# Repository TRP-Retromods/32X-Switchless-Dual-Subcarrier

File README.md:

# 32X-Switchless-Dual-Subcarrier
A single PCB with the Switchless mod and a Dual Subcarrier oscillator for PAL/NTSC Video.

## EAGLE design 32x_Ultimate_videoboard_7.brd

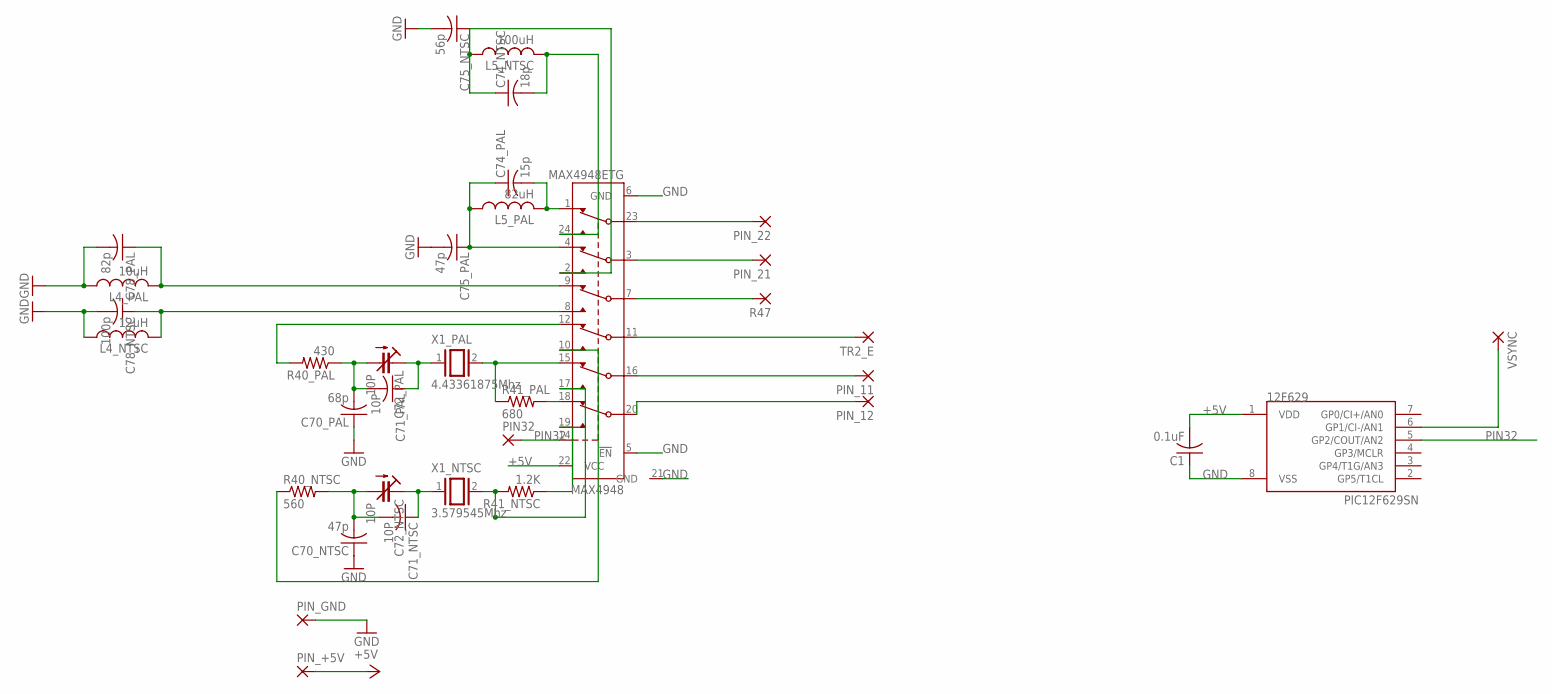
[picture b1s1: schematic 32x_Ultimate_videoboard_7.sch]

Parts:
12F629: PIC12F629SN; SO-08
C1: 0.1uF; C0603
C70_NTSC, C75_PAL: 47p; C0603
C70_PAL: 68p; C0603
C71_NTSC, C71_PAL: 10P; C0603
C72_NTSC, C72_PAL: 10P; CTRIMTZBX4
C74_NTSC: 18p; C0603
C74_PAL: 15p; C0603
C75_NTSC: 56p; C0603
C78_NTSC: 100p; C0603
C78_PAL: 82p; C0603
L4_NTSC: 12uH; L2012C
L4_PAL: 10uH; L2012C
L5_NTSC: 100uH; L2012C
L5_PAL: 82uH; L2012C
MAX4948: MAX4948ETG; TQFN24-EP
PIN32: SMD2; SMD1,27-2,54
PIN_11, PIN_12, PIN_21, PIN_22: SMD2; SMD1,27-2,54
PIN_+5V: SMD5; SMD2,54-5,08
PIN_GND: SMD5; SMD2,54-5,08
R40_NTSC: 560; R0603
R40_PAL: 430; R0603
R41_NTSC: 1.2K; R0603
R41_PAL: 680; R0603
R47: SMD2; SMD1,27-2,54
TR2_E: SMD2; SMD1,27-2,54
VSYNC: SMD2; SMD1,27-2,54
X1_NTSC: 3.579545Mhz; QS
X1_PAL: 4.43361875Mhz; QS

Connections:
+5V: 12F629.1 (VDD), C1.2, MAX4948.22 (VCC), PIN_+5V.1
GND: 12F629.8 (VSS), C1.1, C70_NTSC.1, C70_PAL.1, C75_NTSC.2, C75_PAL.2, C78_NTSC.2, C78_PAL.2, L4_NTSC.1, L4_PAL.1, MAX4948.5 (!EN), MAX4948.6 (GND), MAX4948.21 (GND), PIN_GND.1
unnamed: MAX4948.17 (NO2), R41_NTSC.2, X1_NTSC.2
unnamed: C70_NTSC.2, C71_NTSC.2, C72_NTSC.2 (A), R40_NTSC.2
unnamed: C71_NTSC.1, C72_NTSC.1 (E), X1_NTSC.1
unnamed: MAX4948.20 (COM1), PIN_12.1
unnamed: MAX4948.11 (COM3), TR2_E.1
unnamed: MAX4948.16 (COM2), PIN_11.1
unnamed: MAX4948.18 (NC1), R41_PAL.2
unnamed: MAX4948.12 (NC3), R40_PAL.2
unnamed: MAX4948.19 (NO1), R41_NTSC.1
unnamed: MAX4948.7 (COM4), R47.1
unnamed: C78_PAL.1, L4_PAL.2, MAX4948.9 (NC4)
unnamed: C74_PAL.1, C75_PAL.1, L5_PAL.1, MAX4948.4 (NC5)
unnamed: C70_PAL.2, C71_PAL.2, C72_PAL.2 (A), R40_PAL.1
unnamed: C71_PAL.1, C72_PAL.1 (E), X1_PAL.1
unnamed: 12F629.6 (GP1/CI-/AN1), VSYNC.1
unnamed: C74_PAL.2, L5_PAL.2, MAX4948.1 (NC6)
unnamed: MAX4948.15 (NC2), R41_PAL.1, X1_PAL.2
unnamed: MAX4948.3 (COM5), PIN_21.1
unnamed: MAX4948.23 (COM6), PIN_22.1
unnamed: MAX4948.10 (NO3), R40_NTSC.1
unnamed: C74_NTSC.1, C75_NTSC.1, L5_NTSC.1, MAX4948.2 (NO5)
unnamed: C78_NTSC.1, L4_NTSC.2, MAX4948.8 (NO4)
unnamed: C74_NTSC.2, L5_NTSC.2, MAX4948.24 (NO6)
PIN32: 12F629.5 (GP2/COUT/AN2), MAX4948.14 (CB), PIN32.1

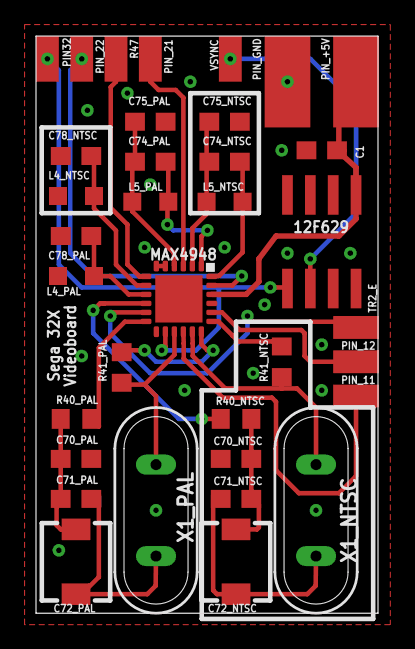
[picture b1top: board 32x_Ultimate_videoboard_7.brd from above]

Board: 2 copper layers, 19.0 x 32.1 mm, 35 parts (0 on the bottom side), 26 nets.

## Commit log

2018-12-27 Add files via upload
    Adding Eagle CAD files and HEX file for the PIC12F629
2019-05-25 Add BOM from Digikey
